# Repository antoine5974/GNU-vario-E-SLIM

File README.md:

# GNU-vario-E-SLIM
Variant of GNU vario E (2,9 inch screen version)
Original project and source : https://prunkdump.github.io/GNUVario-TTGO-T5-website/
Updated PCB (original design by Ratamuse) and new casing design.
The casing is intented for 3D printing with MJF technology, probably not suitable for fused deposit modeling (not tested)

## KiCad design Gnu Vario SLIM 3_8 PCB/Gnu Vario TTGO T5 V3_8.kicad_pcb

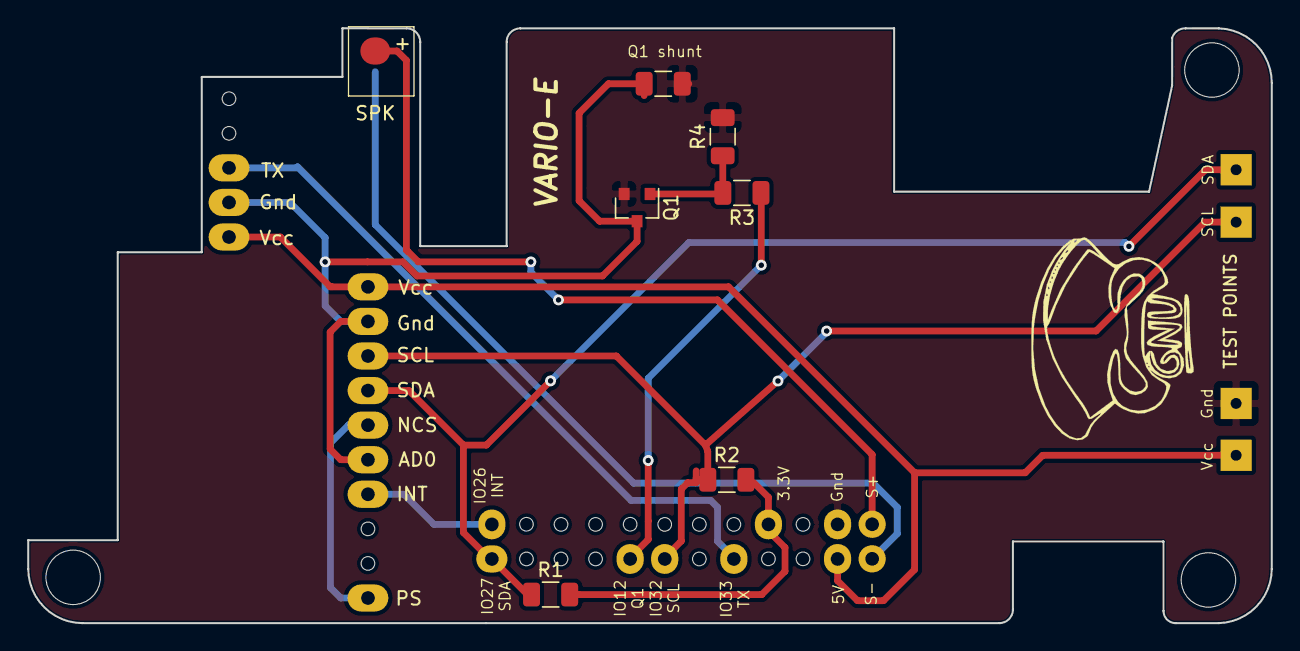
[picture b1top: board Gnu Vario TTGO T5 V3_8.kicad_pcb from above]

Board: 2 copper layers, 91.4 x 43.7 mm, 10 parts (0 on the bottom side), 13 nets.

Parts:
ESP321: TTGO_T5; TTGO_T5_V1.x
LS1: 4-8 ohms; Speaker
Q1: SOT-23; S8050 SOT-23
Q1 shunt: R_1206_3216Metric
R1, R2: 4.7k; R_1206_3216Metric
R3: 1k; R_1206_3216Metric
R4: 10k; R_1206_3216Metric
U1: CJMCU_117; CJMCU-117
U2: ATGM336H; GPS

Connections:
unnamed: ESP321.1, LS1.2
unnamed: ESP321.2, U1.1, U2.1
unnamed: ESP321.5, U2.3
unnamed: ESP321.7, R2.1, U1.3
unnamed: ESP321.8, R3.1
unnamed: ESP321.12, R1.1, U1.4
unnamed: ESP321.13, LS1.1
unnamed: ESP321.14, Q1.2, Q1 shunt.1, R4.2
unnamed: ESP321.16, R1.2, R2.2
unnamed: ESP321.24, U1.7
unnamed: Q1.1, R3.2, R4.1
unnamed: Q1.3, Q1 shunt.2, U1.2, U1.6, U2.2
unnamed: U1.5, U1.10
